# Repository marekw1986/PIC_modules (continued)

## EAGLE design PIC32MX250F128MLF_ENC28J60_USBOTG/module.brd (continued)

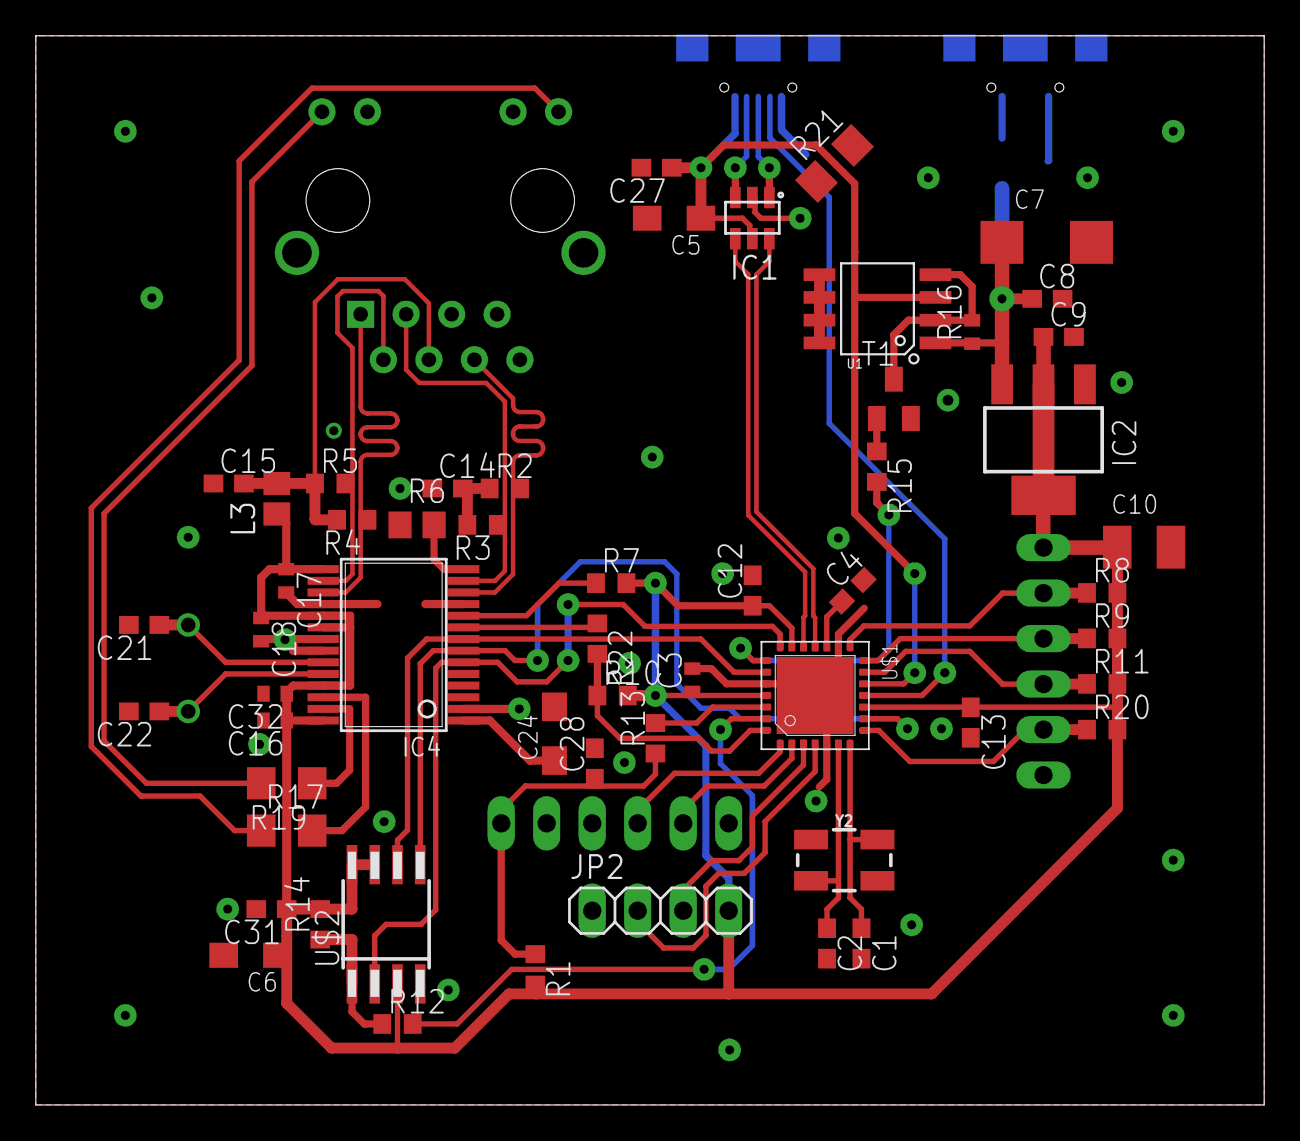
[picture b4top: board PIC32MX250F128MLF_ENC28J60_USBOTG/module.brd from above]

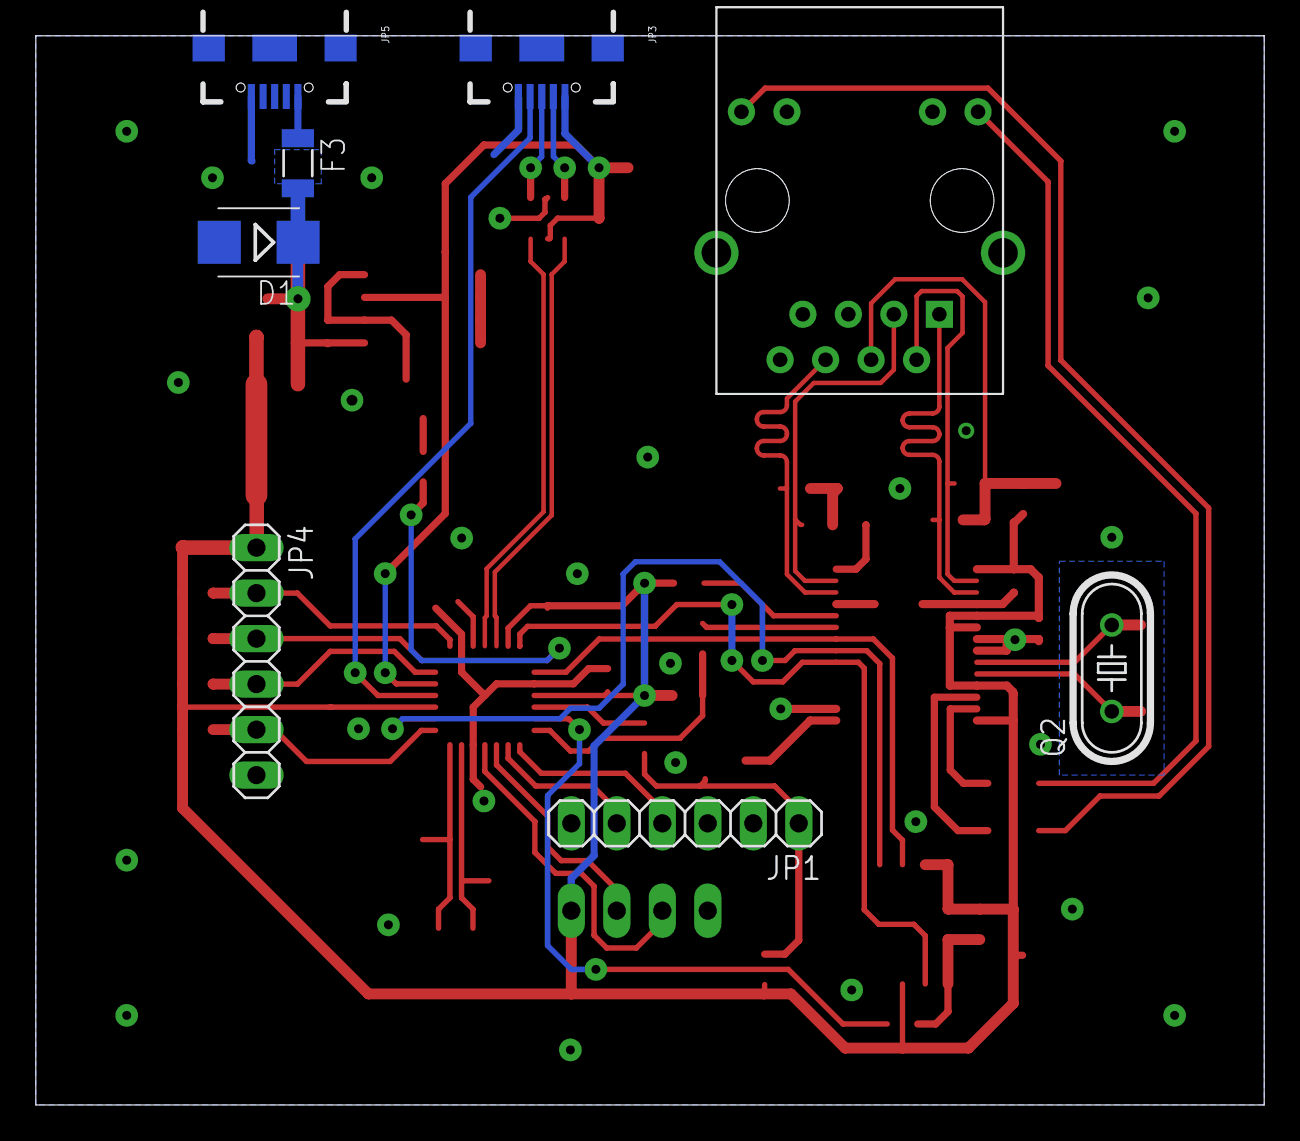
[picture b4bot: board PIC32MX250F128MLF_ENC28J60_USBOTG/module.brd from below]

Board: 2 copper layers, 68.6 x 59.7 mm, 63 parts (8 on the bottom side), 49 nets.

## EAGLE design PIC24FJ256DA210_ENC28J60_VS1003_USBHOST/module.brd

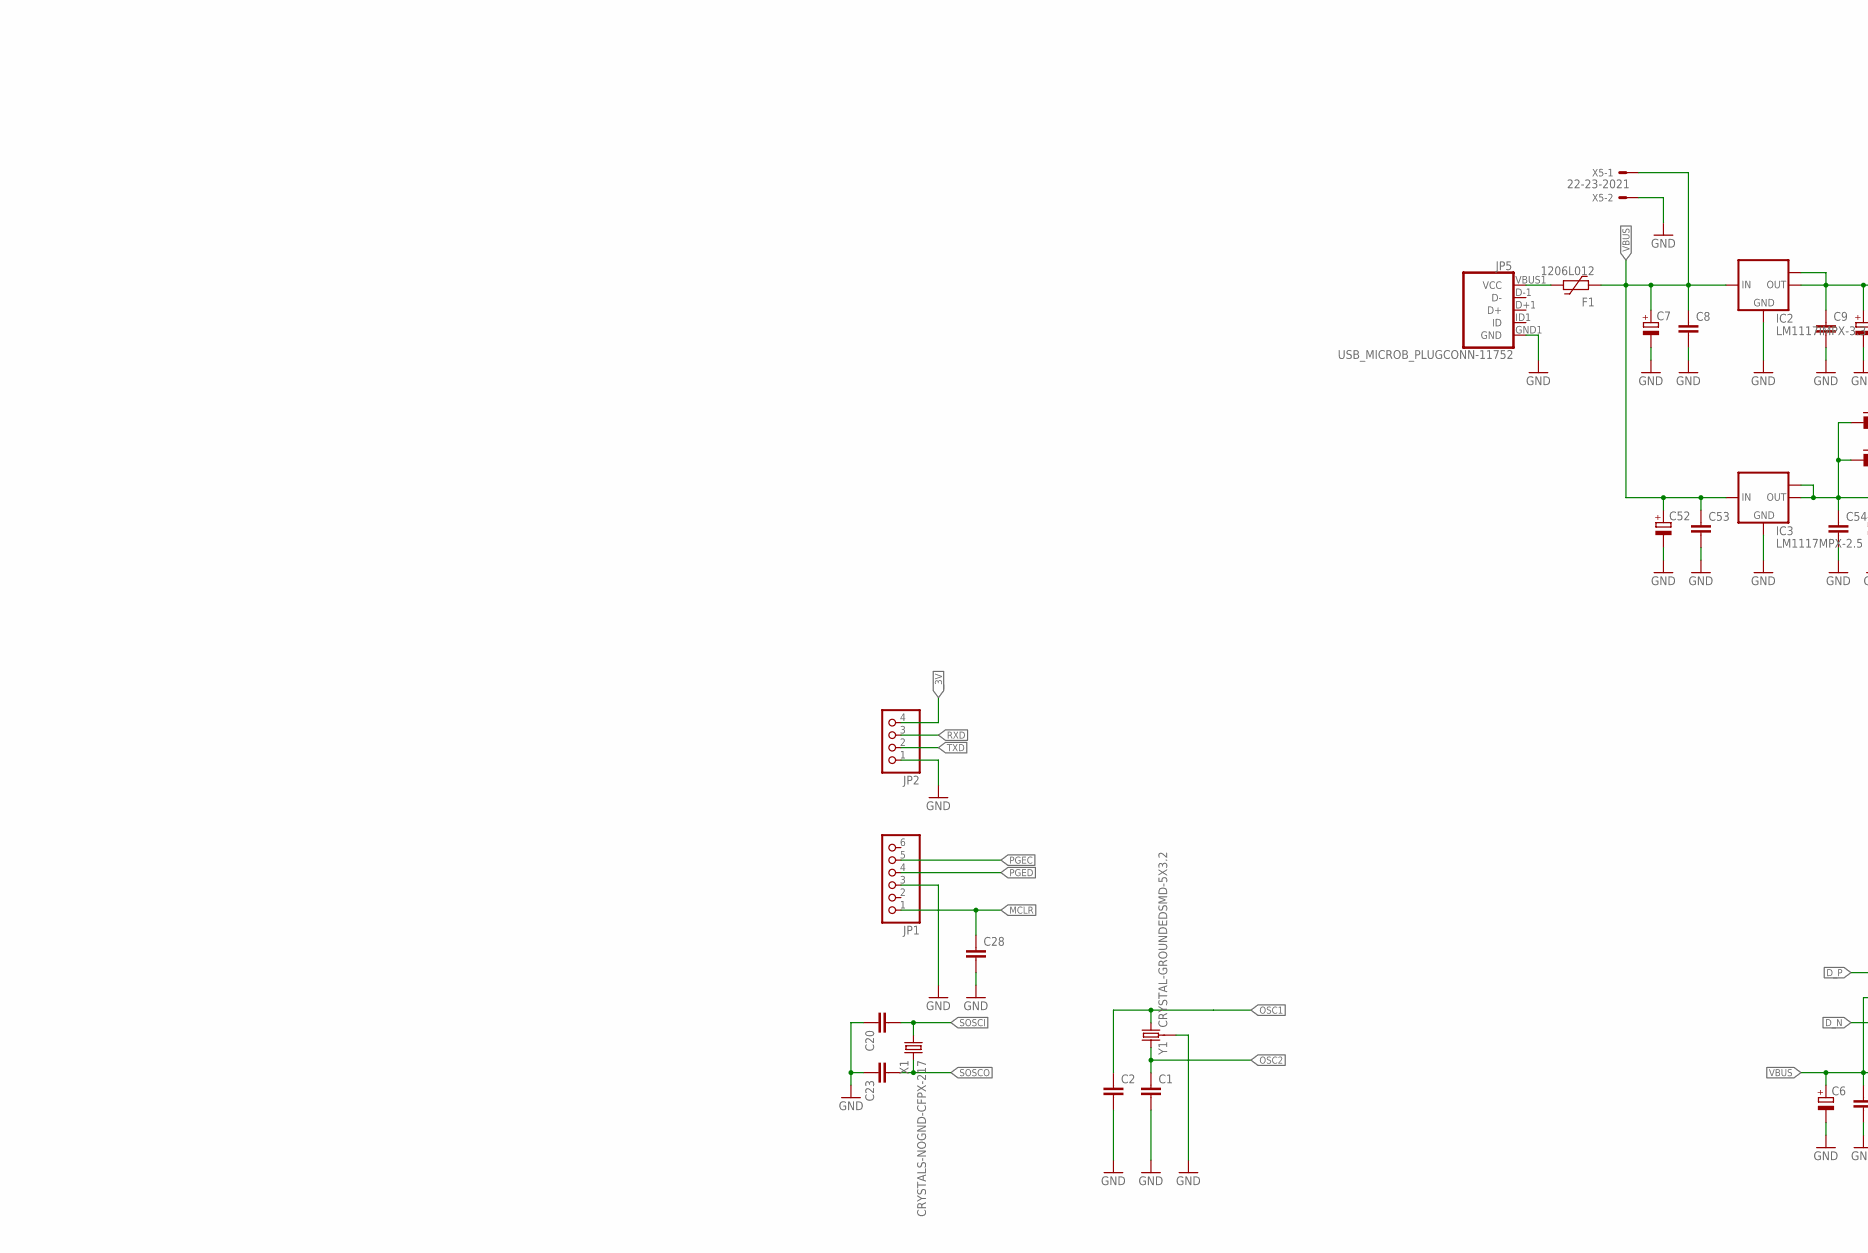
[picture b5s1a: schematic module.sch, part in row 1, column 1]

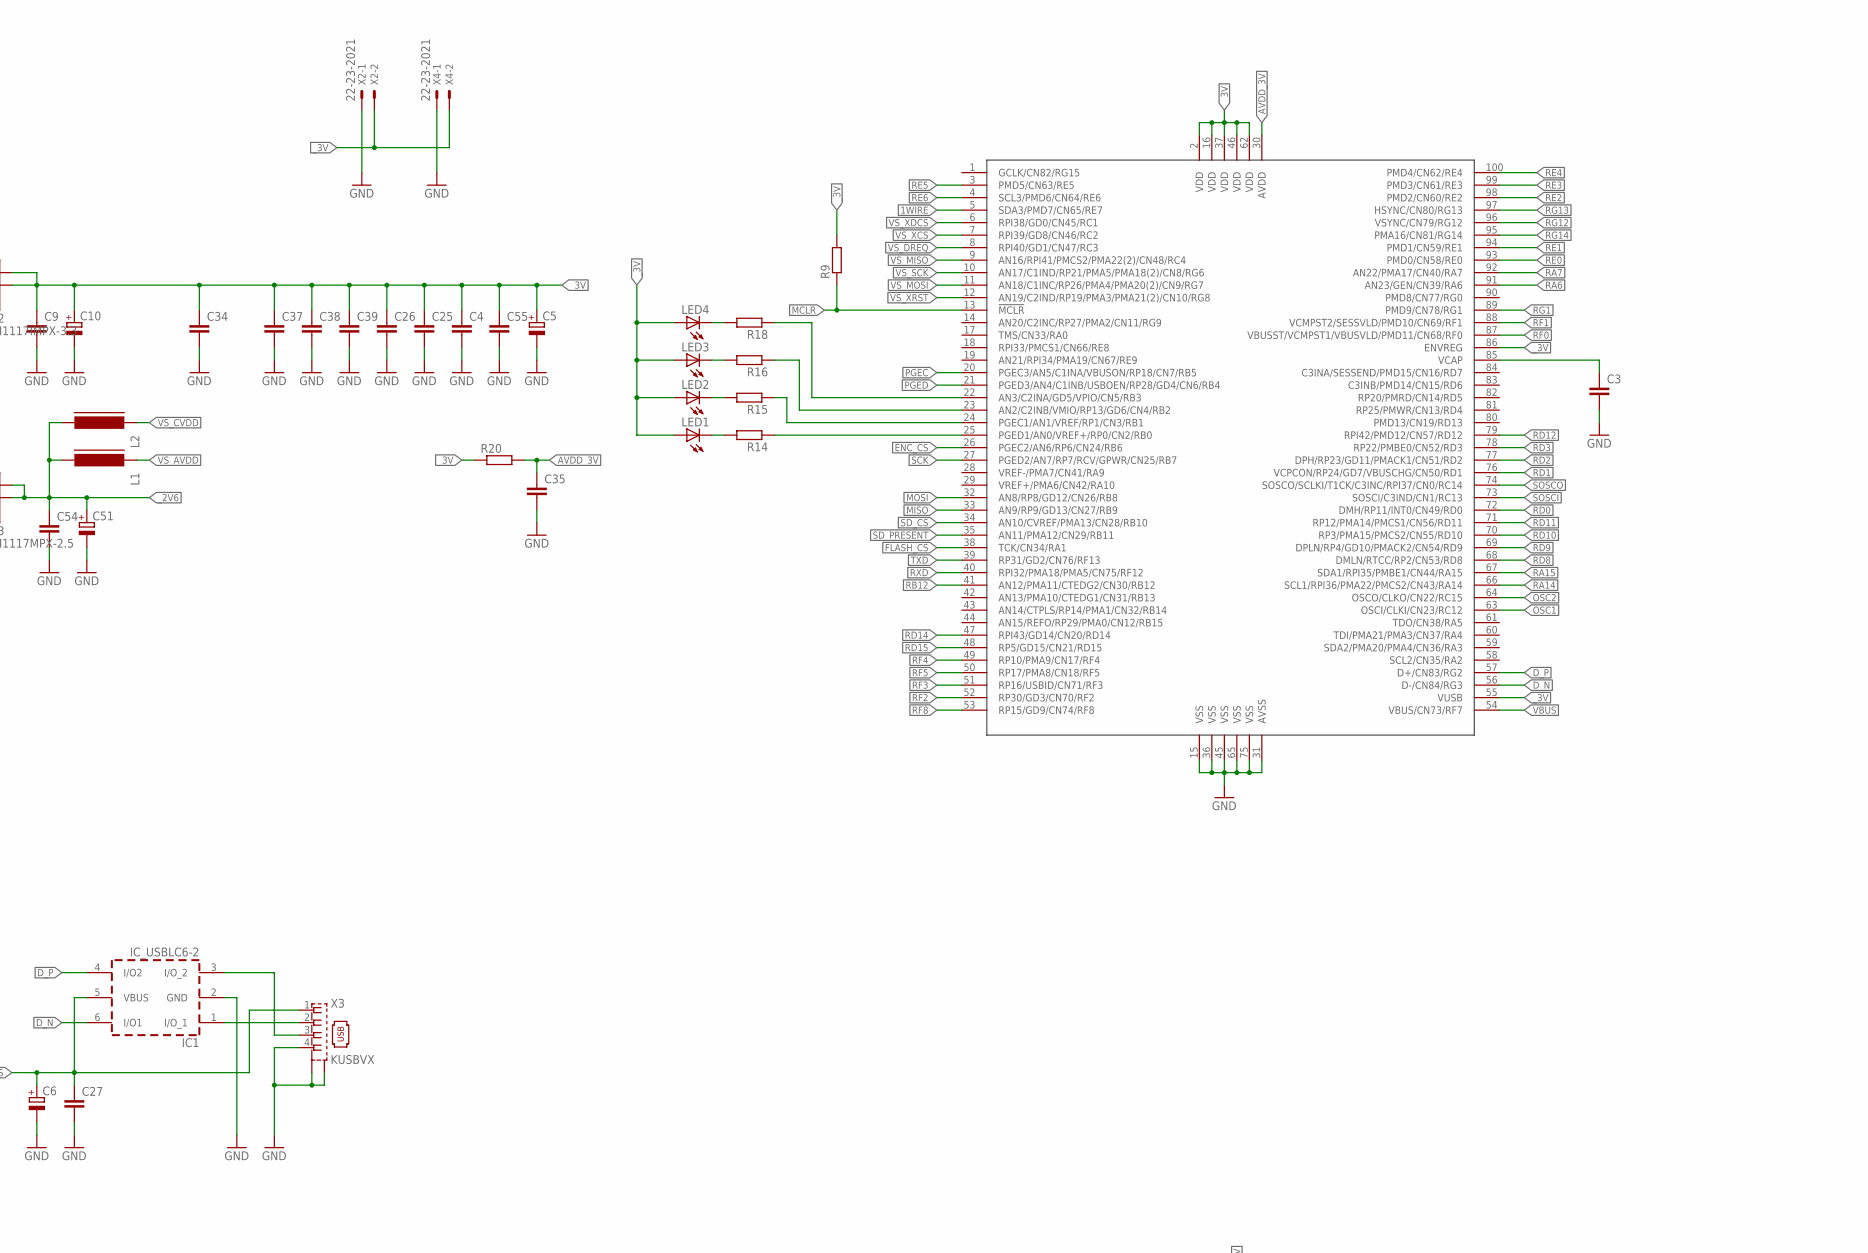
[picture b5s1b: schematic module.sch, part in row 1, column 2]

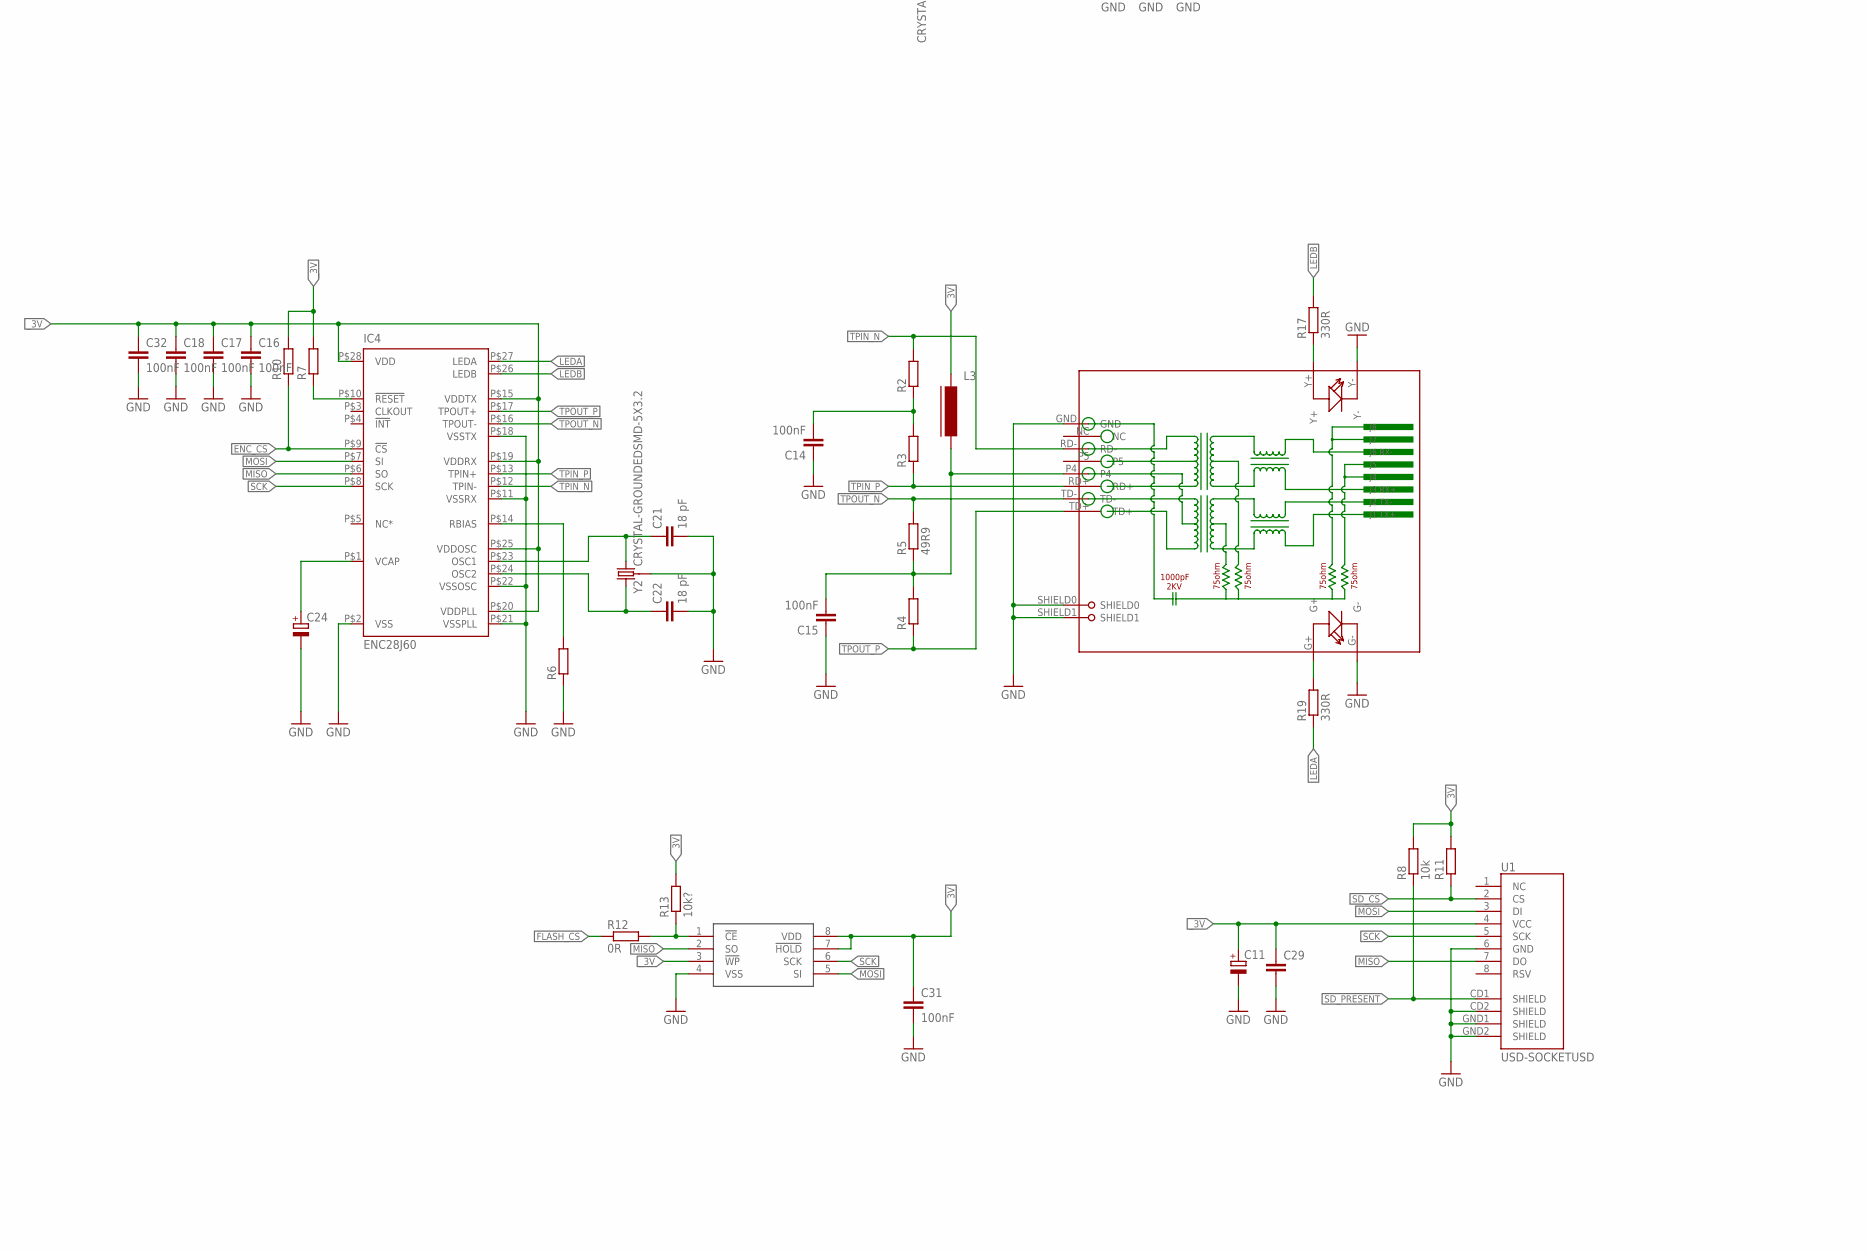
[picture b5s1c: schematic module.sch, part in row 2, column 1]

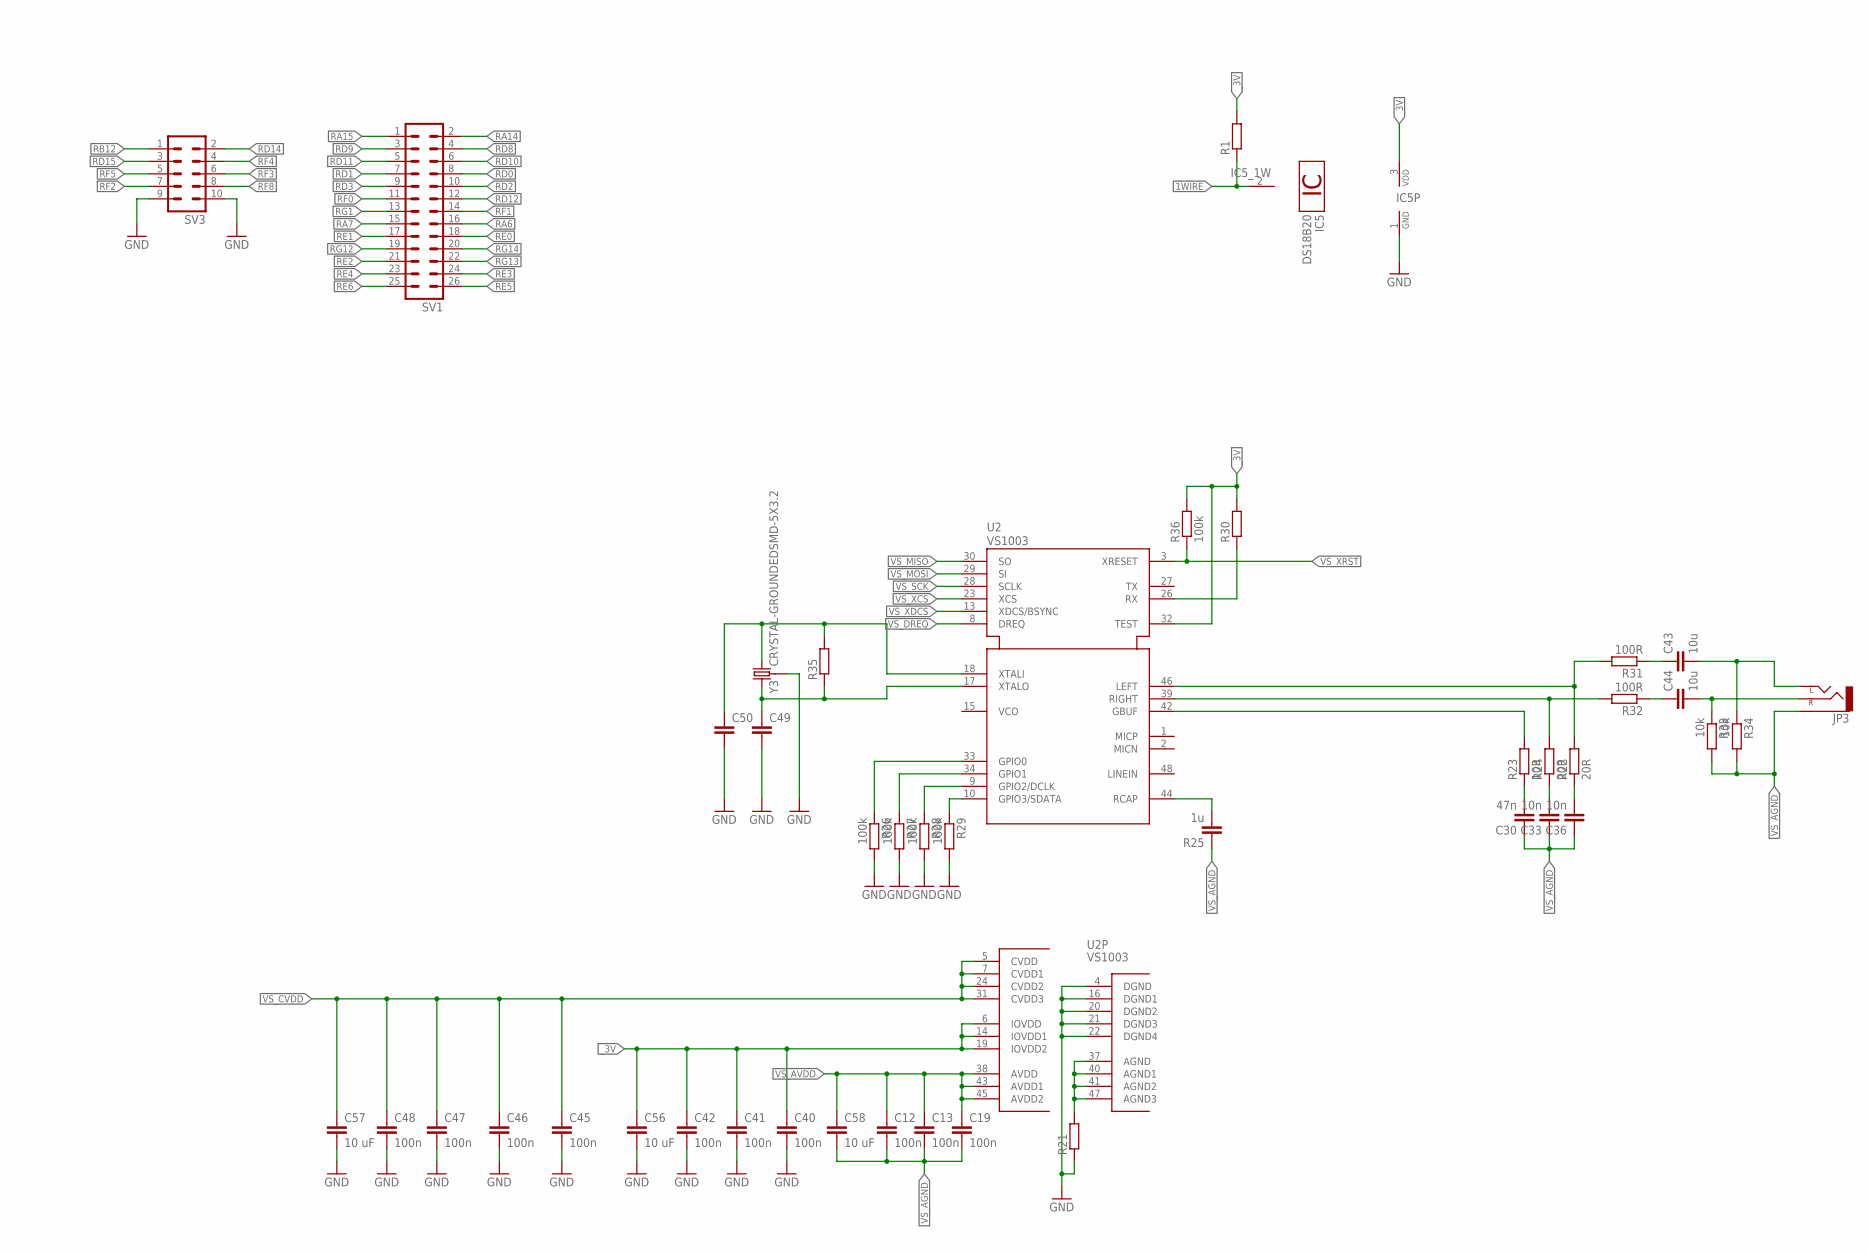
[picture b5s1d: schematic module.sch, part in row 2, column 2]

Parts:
C1, C2, C3, C8, C9, C20, C23, C28, C29, C38, C49, C50, C55: C-EUC0603; C0603
C4, C25, C26, C34, C35, C37, C39: C-EUC0402; C0402
C5, C11, C24: CPOL-EUSMCA; SMC_A
C6, C7, C10: CPOL-EUSMCB; SMC_B
C12, C13, C19, C46, C47, C48: 100n; C0603
C14, C15, C17, C18, C31: 100nF; C0603
C16, C32: 100nF; C0402
C21, C22: 18 pF; C0603
C27: C-EUC0805; C0805
C30: 47n; C0603
C33, C36: 10n; C0603
C40, C41, C42, C45: 100n; C0402
C43, C44: 10u; C0603
C51, C52: CPOL-EUSMCC; SMC_C
C53, C54: C-EUC1206; C1206
C56, C57, C58: 10 uF; C0603
F1: 1206L012; 1206L
IC1: IC_USBLC6-2; SOT-23-6L
IC2: LM1117IMPX-3.3; SOT223
IC3: LM1117MPX-2.5; SOT223
IC4: ENC28J60; TSSOP28W
IC5: DS18B20; TO92-
JP1: PINHD-1X6; 1X06
JP2: PINHD-1X4; 1X04
JP3: AUDIO-JACKAUDIO_JACK2; AUDIO-JACK2
JP5: USB_MICROB_PLUGCONN-11752; USB-B-MICRO-SMD_V03
L1, L2, L3: FERRITE-0805; FB805
LED1, LED2, LED3, LED4: LEDCHIP-LED0603; CHIP-LED0603
R1, R2, R3, R4, R7, R9, R10, R11, R14, R15, R16, R18, R21, R35: R-EU_R0603; R0603
R5: 49R9; R0603
R6, R20: R-EU_R0805; R0805
R8, R33, R34: 10k; R0603
R12: 0R; R0603
R13: 10k?; R0603
R17, R19: 330R; R1206
R22, R24: 20R; R0603
R23: 10R; R0603
R25: 1u; C0603
R26, R27, R28, R29: 100k; R0402
R30: R-EU_0204/7; 0204/7
R31, R32: 100R; R0603
R36: 100k; R0603
RJ1: HR911105A
SV1: ML26L
SV3: ML10L
U1: USD-SOCKETUSD; USD-SOCKET-PP
U2: VS1003; LQFP48
U$1: PIC24FJ256DA210SMALL; TQFP100-12X12
U$2: SST25VF016BSO8M; SO-08M
X1: CRYSTALS-NOGND-CFPX-217; 3.2X1.5-2-PAD
X2, X4, X5: 22-23-2021
X3: KUSBVX
Y1, Y2, Y3: CRYSTAL-GROUNDEDSMD-5X3.2; CRYSTAL-SMD-5X3.2-4PAD

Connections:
1WIRE: IC5.2 (1W), R1.1, U$1.5 (SDA3/PMD7/CN65/RE7)
AVDD_3V: C35.1, R20.2, U$1.30 (AVDD)
CE1: R12.2, R13.1, U$2.1 (!CE)
D2_N: IC1.1 (I/O_1), X3.2
D2_P: IC1.3 (I/O_2), X3.3
D_N: IC1.6 (I/O1), U$1.56 (D-/CN84/RG3)
D_P: IC1.4 (I/O2), U$1.57 (D+/CN83/RG2)
ENC_CS: IC4.P$9 (!CS), R10.1, U$1.26 (PGEC2/AN6/RP6/CN24/RB6)
ENC_RST: IC4.P$10 (!RESET), R7.1
FLASH_CS: R12.1, U$1.38 (TCK/CN34/RA1)
GND: C1.2, C2.2, C3.2, C4.2, C5.-, C6.-, C7.-, C8.2, C9.2, C10.-, C11.-, C14.1, C15.1, C16.2, C17.2, C18.2, C20.1, C21.2, C22.2, C23.1, C24.-, C25.2, C26.2, C27.2, C28.2, C29.2, C31.2, C32.2, C34.2, C35.2, C37.2, C38.2, C39.2, C40.2, C41.2, C42.2, C45.2, C46.2, C47.2, C48.2, C49.2, C50.2, C51.-, C52.-, C53.2, C54.2, C55.2, C56.2, C57.2, IC1.2 (GND), IC2.1 (GND), IC3.1 (GND), IC4.P$2 (VSS), IC4.P$11 (VSSRX), IC4.P$18 (VSSTX), IC4.P$21 (VSSPLL), IC4.P$22 (VSSOSC), IC5.1 (GND), JP1.3, JP2.1, JP5.GND1 (GND), R6.1, R21.1, R26.2, R27.2, R28.2, R29.2, RJ1.G-, RJ1.GND, RJ1.SHIELD0, RJ1.SHIELD1, RJ1.Y-, SV3.9, SV3.10, U1.6 (GND), U1.CD2 (SHIELD), U1.GND1 (SHIELD), U1.GND2 (SHIELD), U2.4 (DGND), U2.16 (DGND1), U2.20 (DGND2), U2.21 (DGND3), U2.22 (DGND4), U$1.15 (VSS), U$1.31 (AVSS), U$1.36 (VSS), U$1.45 (VSS), U$1.65 (VSS), U$1.75 (VSS), U$2.4 (VSS), X2.1, X3.4, X3.M1 (S1), X3.M2 (S2), X4.1, X5.2, Y1.2 (3), Y1.4 (3), Y2.2 (3), Y2.4 (3), Y3.2 (3), Y3.4 (3)
LEDA: IC4.P$27 (LEDA), R19.1
LEDB: IC4.P$26 (LEDB), R17.2
MCLR: C28.1, JP1.1, R9.1, U$1.13 (!MCLR)
MISO: IC4.P$6 (SO), U1.7 (DO), U$1.33 (AN9/RP9/GD13/CN27/RB9), U$2.2 (SO)
MOSI: IC4.P$7 (SI), U1.3 (DI), U$1.32 (AN8/RP8/GD12/CN26/RB8), U$2.5 (SI)
unnamed: C3.1, U$1.85 (VCAP)
unnamed: C14.2, R2.1, R3.2
unnamed: LED1.C, R14.2
unnamed: LED2.C, R15.2
unnamed: C15.2, L3.2, R4.2, R5.1, RJ1.P4
unnamed: LED3.C, R16.2
unnamed: LED4.C, R18.2
unnamed: IC4.P$14 (RBIAS), R6.2
unnamed: F1.1, JP5.VBUS1 (VCC)
unnamed: C30.2, R23.1
unnamed: C21.1, IC4.P$23 (OSC1), Y2.1 (2)
unnamed: C22.1, IC4.P$24 (OSC2), Y2.3 (1)
unnamed: C24.+, IC4.P$1 (VCAP)
unnamed: R17.1, RJ1.Y+
unnamed: R19.2, RJ1.G+
OSC1: C2.1, U$1.63 (OSCI/CLKI/CN23/RC12), Y1.1 (2)
OSC2: C1.1, U$1.64 (OSCO/CLKO/CN22/RC15), Y1.3 (1)
PGEC: JP1.5, U$1.20 (PGEC3/AN5/C1INA/VBUSON/RP18/CN7/RB5)
PGED: JP1.4, U$1.21 (PGED3/AN4/C1INB/USBOEN/RP28/GD4/CN6/RB4)
RA6: SV1.16, U$1.91 (AN23/GEN/CN39/RA6)
RA7: SV1.15, U$1.92 (AN22/PMA17/CN40/RA7)
RA14: SV1.2, U$1.66 (SCL1/RPI36/PMA22/PMCS2/CN43/RA14)
RA15: SV1.1, U$1.67 (SDA1/RPI35/PMBE1/CN44/RA15)
RB0: R14.1, U$1.25 (PGED1/AN0/VREF+/RP0/CN2/RB0)
RB1: R15.1, U$1.24 (PGEC1/AN1/VREF/RP1/CN3/RB1)
RB2: R16.1, U$1.23 (AN2/C2INB/VMIO/RP13/GD6/CN4/RB2)
RB3: R18.1, U$1.22 (AN3/C2INA/GD5/VPIO/CN5/RB3)
RB12: SV3.1, U$1.41 (AN12/PMA11/CTEDG2/CN30/RB12)
RD0: SV1.8, U$1.72 (DMH/RP11/INT0/CN49/RD0)
RD1: SV1.7, U$1.76 (VCPCON/RP24/GD7/VBUSCHG/CN50/RD1)
RD2: SV1.10, U$1.77 (DPH/RP23/GD11/PMACK1/CN51/RD2)
RD3: SV1.9, U$1.78 (RP22/PMBE0/CN52/RD3)
RD8: SV1.4, U$1.68 (DMLN/RTCC/RP2/CN53/RD8)
RD9: SV1.3, U$1.69 (DPLN/RP4/GD10/PMACK2/CN54/RD9)
RD10: SV1.6, U$1.70 (RP3/PMA15/PMCS2/CN55/RD10)
RD11: SV1.5, U$1.71 (RP12/PMA14/PMCS1/CN56/RD11)
RD12: SV1.12, U$1.79 (RPI42/PMD12/CN57/RD12)
RD14: SV3.2, U$1.47 (RPI43/GD14/CN20/RD14)
RD15: SV3.3, U$1.48 (RP5/GD15/CN21/RD15)
RE0: SV1.18, U$1.93 (PMD0/CN58/RE0)
RE1: SV1.17, U$1.94 (PMD1/CN59/RE1)
RE2: SV1.21, U$1.98 (PMD2/CN60/RE2)
RE3: SV1.24, U$1.99 (PMD3/CN61/RE3)
RE4: SV1.23, U$1.100 (PMD4/CN62/RE4)
RE5: SV1.26, U$1.3 (PMD5/CN63/RE5)
RE6: SV1.25, U$1.4 (SCL3/PMD6/CN64/RE6)
RF0: SV1.11, U$1.87 (VBUSST/VCMPST1/VBUSVLD/PMD11/CN68/RF0)
RF1: SV1.14, U$1.88 (VCMPST2/SESSVLD/PMD10/CN69/RF1)
RF2: SV3.7, U$1.52 (RP30/GD3/CN70/RF2)
RF3: SV3.6, U$1.51 (RP16/USBID/CN71/RF3)
RF4: SV3.4, U$1.49 (RP10/PMA9/CN17/RF4)
RF5: SV3.5, U$1.50 (RP17/PMA8/CN18/RF5)
RF8: SV3.8, U$1.53 (RP15/GD9/CN74/RF8)
RG1: SV1.13, U$1.89 (PMD9/CN78/RG1)
RG12: SV1.19, U$1.96 (VSYNC/CN79/RG12)
RG13: SV1.22, U$1.97 (HSYNC/CN80/RG13)
RG14: SV1.20, U$1.95 (PMA16/CN81/RG14)
RXD: JP2.3, U$1.40 (RPI32/PMA18/PMA5/CN75/RF12)
SCK: IC4.P$8 (SCK), U1.5 (SCK), U$1.27 (PGED2/AN7/RP7/RCV/GPWR/CN25/RB7), U$2.6 (SCK)
SD_CS: R11.1, U1.2 (CS), U$1.34 (AN10/CVREF/PMA13/CN28/RB10)
SD_PRESENT: R8.1, U1.CD1 (SHIELD), U$1.35 (AN11/PMA12/CN29/RB11)
SOSCI: C20.2, U$1.73 (SOSCI/C3IND/CN1/RC13), X1.1
SOSCO: C23.2, U$1.74 (SOSCO/SCLKI/T1CK/C3INC/RPI37/CN0/RC14), X1.2
TPIN_N: IC4.P$12 (TPIN-), R2.2, RJ1.RD-
TPIN_P: IC4.P$13 (TPIN+), R3.1, RJ1.RD+
TPOUT_N: IC4.P$16 (TPOUT-), R5.2, RJ1.TD-
TPOUT_P: IC4.P$17 (TPOUT+), R4.1, RJ1.TD+
TXD: JP2.2, U$1.39 (RP31/GD2/CN76/RF13)
VBUS: C6.+, C7.+, C8.1, C27.1, C52.+, C53.1, F1.2, IC1.5 (VBUS), IC2.3 (IN), IC3.3 (IN), U$1.54 (VBUS/CN73/RF7), X3.1, X5.1
VS_AGND: C12.2, C13.2, C19.2, C30.1, C33.1, C36.1, C58.2, JP3.SLEEVE, R21.2, R25.1, R33.2, R34.2, U2.37 (AGND), U2.40 (AGND1), U2.41 (AGND2), U2.47 (AGND3)
VS_AVDD: C12.1, C13.1, C19.1, C58.1, L1.1, U2.38 (AVDD), U2.43 (AVDD1), U2.45 (AVDD2)
VS_CVDD: C45.1, C46.1, C47.1, C48.1, C57.1, L2.1, U2.5 (CVDD), U2.7 (CVDD1), U2.24 (CVDD2), U2.31 (CVDD3)
VS_DREQ: U2.8 (DREQ), U$1.8 (RPI40/GD1/CN47/RC3)
VS_MISO: U2.30 (SO), U$1.9 (AN16/RPI41/PMCS2/PMA22(2)/CN48/RC4)
VS_MOSI: U2.29 (SI), U$1.11 (AN18/C1INC/RP26/PMA4/PMA20(2)/CN9/RG7)
VS_N$9: C50.1, R35.2, U2.18 (XTALI), Y3.1 (2)
VS_N$13: C49.1, R35.1, U2.17 (XTALO), Y3.3 (1)
VS_N$14: R22.2, R31.2, U2.46 (LEFT)
VS_N$15: R23.2, U2.42 (GBUF)
VS_N$16: R24.2, R32.2, U2.39 (RIGHT)
VS_N$17: R25.2, U2.44 (RCAP)
VS_N$24: C33.2, R24.1
VS_N$25: C36.2, R22.1
VS_N$26: R29.1, U2.10 (GPIO3/SDATA)
VS_N$27: R28.1, U2.9 (GPIO2/DCLK)
VS_N$28: R27.1, U2.34 (GPIO1)
VS_N$30: R26.1, U2.33 (GPIO0)
VS_N$34: R30.1, U2.26 (RX)
VS_N$35: C43.1, R31.1
VS_N$36: C44.1, R32.1
VS_N$37: C44.2, JP3.RING (RIGHT), R33.1
VS_N$38: C43.2, JP3.TIP (LEFT), R34.1
VS_SCK: U2.28 (SCLK), U$1.10 (AN17/C1IND/RP21/PMA5/PMA18(2)/CN8/RG6)
VS_XCS: U2.23 (XCS), U$1.7 (RPI39/GD8/CN46/RC2)
VS_XDCS: U2.13 (XDCS/BSYNC), U$1.6 (RPI38/GD0/CN45/RC1)
VS_XRST: R36.1, U2.3 (XRESET), U$1.12 (AN19/C2IND/RP19/PMA3/PMA21(2)/CN10/RG8)
_2V6: C51.+, C54.1, IC3.2 (OUT), IC3.TAB (OUT1), L1.2, L2.2
_3V: C4.1, C5.+, C9.1, C10.+, C11.+, C16.1, C17.1, C18.1, C25.1, C26.1, C29.1, C31.1, C32.1, C34.1, C37.1, C38.1, C39.1, C40.1, C41.1, C42.1, C55.1, C56.1, IC2.2 (OUT), IC2.TAB (OUT1), IC4.P$15 (VDDTX), IC4.P$19 (VDDRX), IC4.P$20 (VDDPLL), IC4.P$25 (VDDOSC), IC4.P$28 (VDD), IC5.3 (VDD), JP2.4, L3.1, LED1.A, LED2.A, LED3.A, LED4.A, R1.2, R7.2, R8.2, R9.2, R10.2, R11.2, R13.2, R20.1, R30.2, R36.2, U1.4 (VCC), U2.6 (IOVDD), U2.14 (IOVDD1), U2.19 (IOVDD2), U2.32 (TEST), U$1.2 (VDD), U$1.16 (VDD), U$1.37 (VDD), U$1.46 (VDD), U$1.55 (VUSB), U$1.62 (VDD), U$1.86 (ENVREG), U$2.3 (!WP), U$2.7 (!HOLD), U$2.8 (VDD), X2.2, X4.2

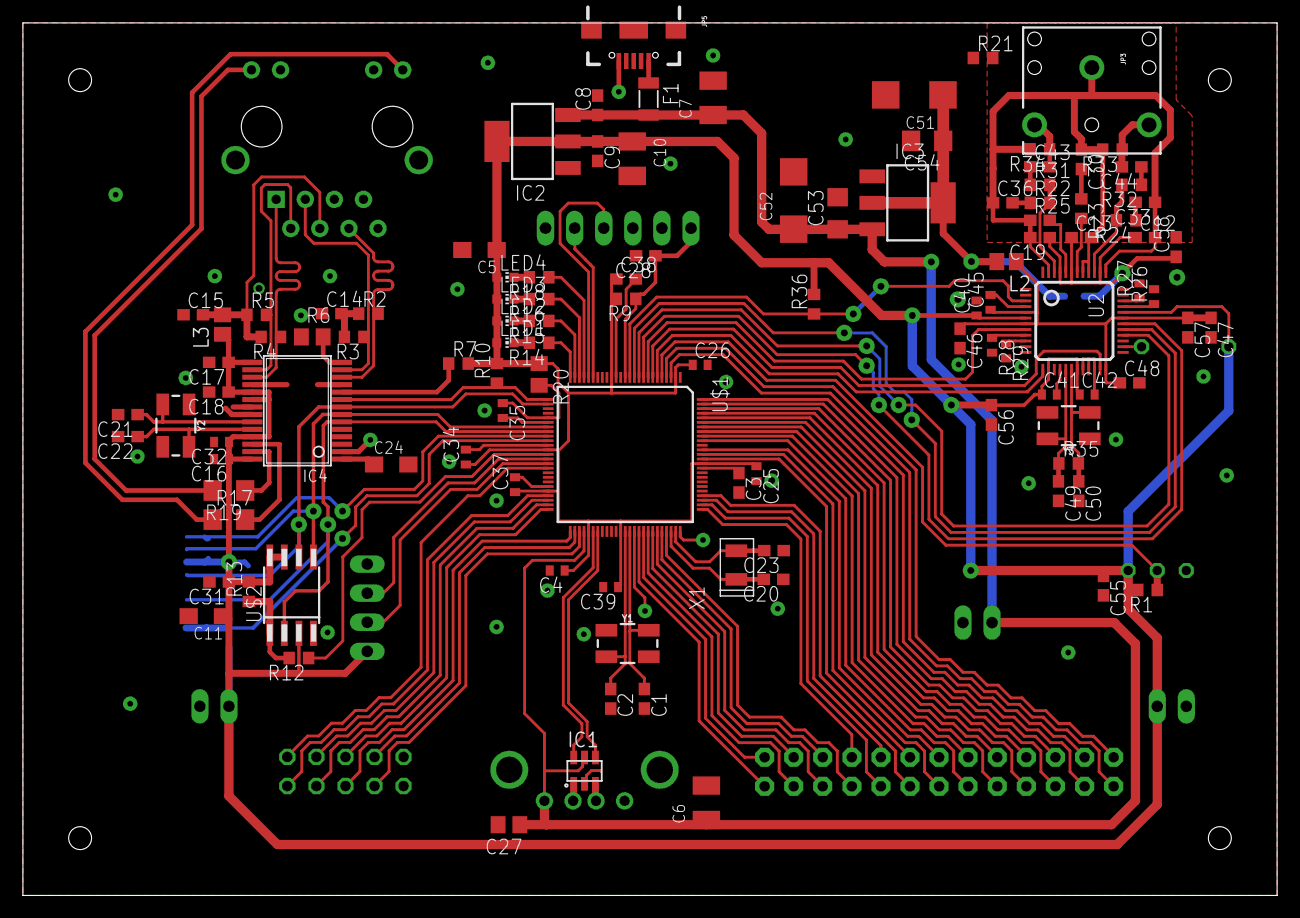
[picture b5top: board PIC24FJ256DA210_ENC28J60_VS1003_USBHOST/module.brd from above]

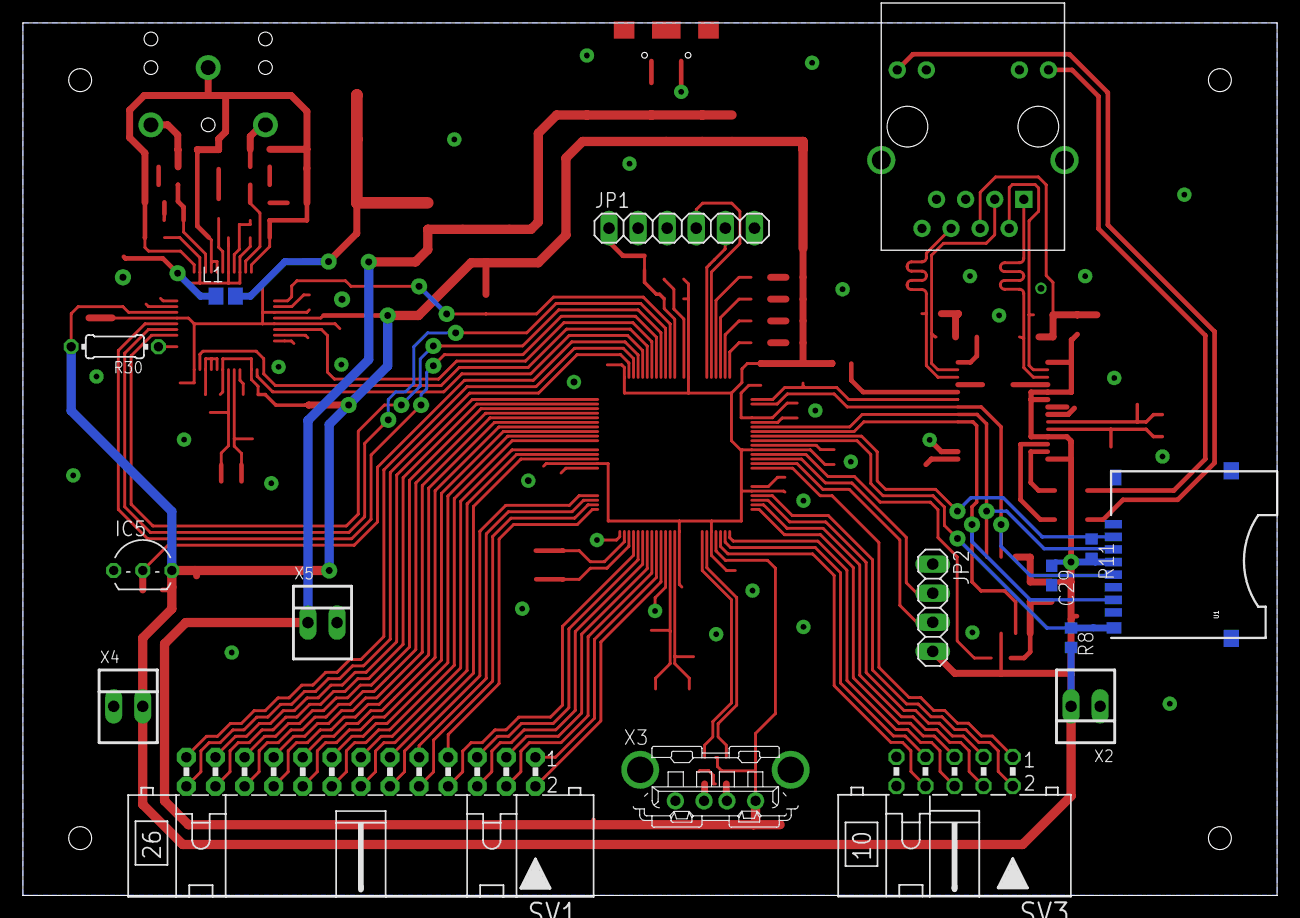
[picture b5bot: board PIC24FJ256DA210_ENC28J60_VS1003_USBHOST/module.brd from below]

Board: 2 copper layers, 109.5 x 76.2 mm, 126 parts (16 on the bottom side), 114 nets.
